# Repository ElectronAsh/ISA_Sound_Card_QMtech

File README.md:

# FPGA-based ISA Sound Card

Warning: Please don't build this yet. It's not 100% done, and no PCBs have been ordered yet.

The idea here is to leverage the Sound Blaster 16 and OPL Verilog from the ao486 project to use on an ISA card.
In theory, it shouldn't take too much effort to adapt that logic to run on a "real" ISA bus, but I may be speaking too soon. lol

(ao486 and OPL3 cores by Aleksander Osman. Improvements by Sorgelig, Robert Piep, and many others.) 

This version is using the Cyclone IV module from QMtech...

https://www.aliexpress.com/item/32949281189.html

This is mainly due to the current chip shortage, and there aren't many of the QMtech boards left in stock either.

If/when the chip shortage improves, the FPGA can be put directly onto the ISA card.

There are some sellers on AliExpress who have the very same FPGA available, but their stock levels also might be quite low.

Using the QMtech board does save from having to do the BGA routing for the FPGA, and the routing for the SDRAM.
The modules also have switching regulators onboard, for the FPGA and 3V3 rails.

The SDRAM will be useful for trying my old Wavetable MIDI synth later.

Shoutout to the RMC crew on Discord. ;)

ElectronAsh

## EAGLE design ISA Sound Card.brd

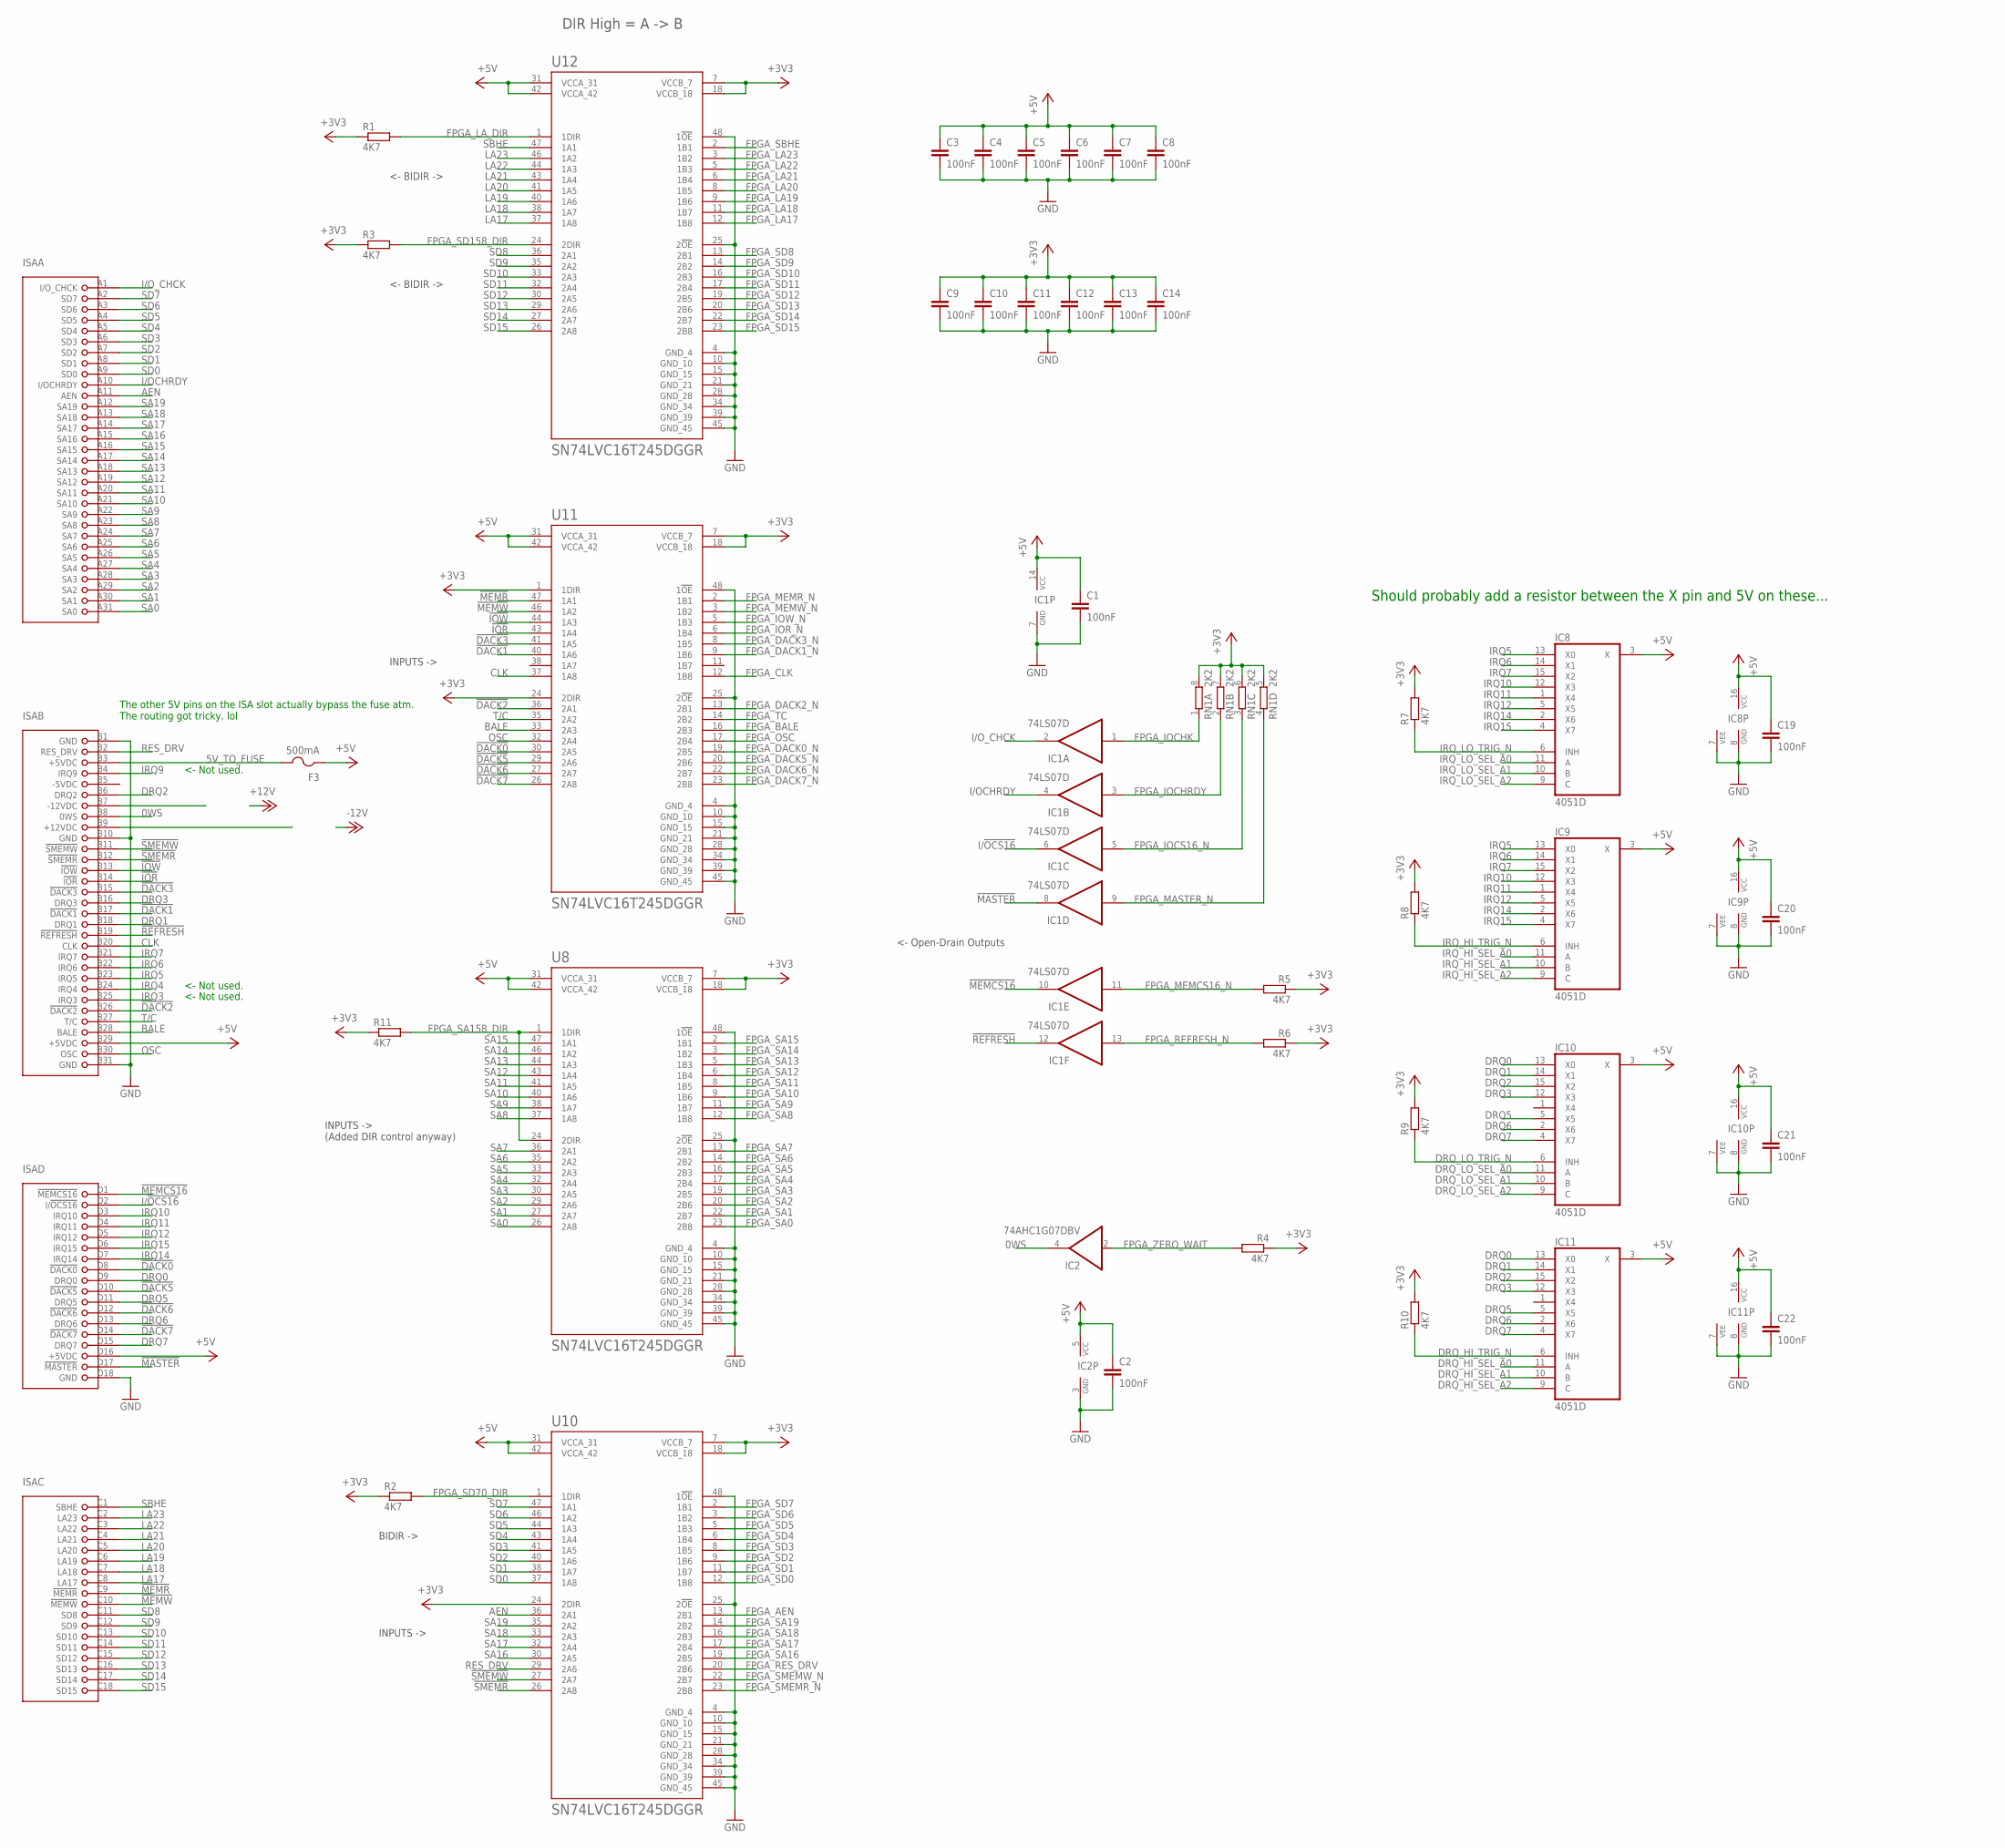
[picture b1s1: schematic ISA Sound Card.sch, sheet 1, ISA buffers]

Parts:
C1, C2, C3, C4, C5, C6, C7, C8, C9, C10, C11, C12, C13, C14, C19, C20, C21, C22: 100nF; C0603
F3: 500mA; R1206
IC1: 74LS07D; SO14
IC2: 74AHC1G07DBV; SOT23-5
IC8, IC9, IC10, IC11: 4051D; SO16
ISA: IBMATBUS; IBM-AT
R1, R2, R3, R4, R5, R6, R7, R8, R9, R10, R11: 4K7; R0603
RN1: 2K2; 0603-ARC
U8, U10, U11, U12: SN74LVC16T245DGGR; SOP50P810X120-48N

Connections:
0WS: IC2.4 (O), ISA.B8 (0WS)
5V_TO_FUSE: F3.2, ISA.B3 (+5VDC)
!DACK0: ISA.D8 (!DACK0), U11.30 (2A5)
!DACK1: ISA.B17 (!DACK1), U11.40 (1A6)
!DACK2: ISA.B26 (!DACK2), U11.36 (2A1)
!DACK3: ISA.B15 (!DACK3), U11.41 (1A5)
!DACK5: ISA.D10 (!DACK5), U11.29 (2A6)
!DACK6: ISA.D12 (!DACK6), U11.27 (2A7)
!DACK7: ISA.D14 (!DACK7), U11.26 (2A8)
!IOR: ISA.B14 (!IOR), U11.43 (1A4)
!IOW: ISA.B13 (!IOW), U11.44 (1A3)
!MASTER: IC1.8 (O), ISA.D17 (!MASTER)
!MEMCS16: IC1.10 (O), ISA.D1 (!MEMCS16)
!MEMR: ISA.C9 (!MEMR), U11.47 (1A1)
!MEMW: ISA.C10 (!MEMW), U11.46 (1A2)
!REFRESH: IC1.12 (O), ISA.B19 (!REFRESH)
!SMEMR: ISA.B12 (!SMEMR), U10.26 (2A8)
!SMEMW: ISA.B11 (!SMEMW), U10.27 (2A7)
+3V3: C9.1, C10.1, C11.1, C12.1, C13.1, C14.1, R1.1, R2.1, R3.1, R4.1, R5.1, R6.1, R7.2, R8.2, R9.2, R10.2, R11.1, RN1.5 (2), RN1.6 (2), RN1.7 (2), RN1.8 (2), U8.7 (VCCB_7), U8.18 (VCCB_18), U10.7 (VCCB_7), U10.18 (VCCB_18), U10.24 (2DIR), U11.1 (1DIR), U11.7 (VCCB_7), U11.18 (VCCB_18), U11.24 (2DIR), U12.7 (VCCB_7), U12.18 (VCCB_18); also elsewhere on the board
+5V: C1.1, C2.1, C3.1, C4.1, C5.1, C6.1, C7.1, C8.1, C19.1, C20.1, C21.1, C22.1, F3.1, IC1.14 (VCC), IC2.5 (VCC), IC8.3 (X), IC8.16 (VCC), IC9.3 (X), IC9.16 (VCC), IC10.3 (X), IC10.16 (VCC), IC11.3 (X), IC11.16 (VCC), ISA.B29 (+5VDC), ISA.D16 (+5VDC), U8.31 (VCCA_31), U8.42 (VCCA_42), U10.31 (VCCA_31), U10.42 (VCCA_42), U11.31 (VCCA_31), U11.42 (VCCA_42), U12.31 (VCCA_31), U12.42 (VCCA_42); also elsewhere on the board
-5VDC: ISA.B5 (-5VDC)
AEN: ISA.A11 (AEN), U10.36 (2A1)
BALE: ISA.B28 (BALE), U11.33 (2A3)
CLK: ISA.B20 (CLK), U11.37 (1A8)
DRQ0: IC10.13 (X0), IC11.13 (X0), ISA.D9 (DRQ0)
DRQ1: IC10.14 (X1), IC11.14 (X1), ISA.B18 (DRQ1)
DRQ2: IC10.15 (X2), IC11.15 (X2), ISA.B6 (DRQ2)
DRQ3: IC10.12 (X3), IC11.12 (X3), ISA.B16 (DRQ3)
DRQ5: IC10.5 (X5), IC11.5 (X5), ISA.D11 (DRQ5)
DRQ6: IC10.2 (X6), IC11.2 (X6), ISA.D13 (DRQ6)
DRQ7: IC10.4 (X7), IC11.4 (X7), ISA.D15 (DRQ7)
DRQ_HI_SEL_A0: IC11.11 (A); also elsewhere on the board
DRQ_HI_SEL_A1: IC11.10 (B); also elsewhere on the board
DRQ_HI_SEL_A2: IC11.9 (C); also elsewhere on the board
DRQ_HI_TRIG_N: IC11.6 (INH), R10.1; also elsewhere on the board
DRQ_LO_SEL_A0: IC10.11 (A); also elsewhere on the board
DRQ_LO_SEL_A1: IC10.10 (B); also elsewhere on the board
DRQ_LO_SEL_A2: IC10.9 (C); also elsewhere on the board
DRQ_LO_TRIG_N: IC10.6 (INH), R9.1; also elsewhere on the board
FPGA_AEN: U10.13 (2B1); also elsewhere on the board
FPGA_BALE: U11.16 (2B3); also elsewhere on the board
FPGA_CLK: U11.12 (1B8); also elsewhere on the board
FPGA_DACK0_N: U11.19 (2B5); also elsewhere on the board
FPGA_DACK1_N: U11.9 (1B6); also elsewhere on the board
FPGA_DACK2_N: U11.13 (2B1); also elsewhere on the board
FPGA_DACK3_N: U11.8 (1B5); also elsewhere on the board
FPGA_DACK5_N: U11.20 (2B6); also elsewhere on the board
FPGA_DACK6_N: U11.22 (2B7); also elsewhere on the board
FPGA_DACK7_N: U11.23 (2B8); also elsewhere on the board
FPGA_IOCHK: IC1.1 (I), RN1.1; also elsewhere on the board
FPGA_IOCHRDY: IC1.3 (I), RN1.2 (1); also elsewhere on the board
FPGA_IOCS16_N: IC1.5 (I), RN1.3 (1); also elsewhere on the board
FPGA_IOR_N: U11.6 (1B4); also elsewhere on the board
FPGA_IOW_N: U11.5 (1B3); also elsewhere on the board
FPGA_LA17: U12.12 (1B8); also elsewhere on the board
FPGA_LA18: U12.11 (1B7); also elsewhere on the board
FPGA_LA19: U12.9 (1B6); also elsewhere on the board
FPGA_LA20: U12.8 (1B5); also elsewhere on the board
FPGA_LA21: U12.6 (1B4); also elsewhere on the board
FPGA_LA22: U12.5 (1B3); also elsewhere on the board
FPGA_LA23: U12.3 (1B2); also elsewhere on the board
FPGA_LA_DIR: R1.2, U12.1 (1DIR); also elsewhere on the board
FPGA_MASTER_N: IC1.9 (I), RN1.4 (1); also elsewhere on the board
FPGA_MEMCS16_N: IC1.11 (I), R5.2; also elsewhere on the board
FPGA_MEMR_N: U11.2 (1B1); also elsewhere on the board
FPGA_MEMW_N: U11.3 (1B2); also elsewhere on the board
FPGA_OSC: U11.17 (2B4); also elsewhere on the board
FPGA_REFRESH_N: IC1.13 (I), R6.2; also elsewhere on the board
FPGA_RES_DRV: U10.20 (2B6); also elsewhere on the board
FPGA_SA0: U8.23 (2B8); also elsewhere on the board
FPGA_SA1: U8.22 (2B7); also elsewhere on the board
FPGA_SA2: U8.20 (2B6); also elsewhere on the board
FPGA_SA3: U8.19 (2B5); also elsewhere on the board
FPGA_SA4: U8.17 (2B4); also elsewhere on the board
FPGA_SA5: U8.16 (2B3); also elsewhere on the board
FPGA_SA6: U8.14 (2B2); also elsewhere on the board
FPGA_SA7: U8.13 (2B1); also elsewhere on the board
FPGA_SA8: U8.12 (1B8); also elsewhere on the board
FPGA_SA9: U8.11 (1B7); also elsewhere on the board
FPGA_SA10: U8.9 (1B6); also elsewhere on the board
FPGA_SA11: U8.8 (1B5); also elsewhere on the board
FPGA_SA12: U8.6 (1B4); also elsewhere on the board
FPGA_SA13: U8.5 (1B3); also elsewhere on the board
FPGA_SA14: U8.3 (1B2); also elsewhere on the board
FPGA_SA15: U8.2 (1B1); also elsewhere on the board
FPGA_SA16: U10.19 (2B5); also elsewhere on the board
FPGA_SA17: U10.17 (2B4); also elsewhere on the board
FPGA_SA18: U10.16 (2B3); also elsewhere on the board
FPGA_SA19: U10.14 (2B2); also elsewhere on the board
FPGA_SA158_DIR: R11.2, U8.1 (1DIR), U8.24 (2DIR); also elsewhere on the board
FPGA_SBHE: U12.2 (1B1); also elsewhere on the board
FPGA_SD0: U10.12 (1B8); also elsewhere on the board
FPGA_SD1: U10.11 (1B7); also elsewhere on the board
FPGA_SD2: U10.9 (1B6); also elsewhere on the board
FPGA_SD3: U10.8 (1B5); also elsewhere on the board
FPGA_SD4: U10.6 (1B4); also elsewhere on the board
FPGA_SD5: U10.5 (1B3); also elsewhere on the board
FPGA_SD6: U10.3 (1B2); also elsewhere on the board
FPGA_SD7: U10.2 (1B1); also elsewhere on the board
FPGA_SD8: U12.13 (2B1); also elsewhere on the board
FPGA_SD9: U12.14 (2B2); also elsewhere on the board
FPGA_SD10: U12.16 (2B3); also elsewhere on the board
FPGA_SD11: U12.17 (2B4); also elsewhere on the board
FPGA_SD12: U12.19 (2B5); also elsewhere on the board
FPGA_SD13: U12.20 (2B6); also elsewhere on the board
FPGA_SD14: U12.22 (2B7); also elsewhere on the board
FPGA_SD15: U12.23 (2B8); also elsewhere on the board
FPGA_SD70_DIR: R2.2, U10.1 (1DIR); also elsewhere on the board
FPGA_SD158_DIR: R3.2, U12.24 (2DIR); also elsewhere on the board
FPGA_SMEMR_N: U10.23 (2B8); also elsewhere on the board
FPGA_SMEMW_N: U10.22 (2B7); also elsewhere on the board
FPGA_TC: U11.14 (2B2); also elsewhere on the board
FPGA_ZERO_WAIT: IC2.2 (I), R4.2; also elsewhere on the board
GND: C1.2, C2.2, C3.2, C4.2, C5.2, C6.2, C7.2, C8.2, C9.2, C10.2, C11.2, C12.2, C13.2, C14.2, C19.2, C20.2, C21.2, C22.2, IC1.7 (GND), IC2.3 (GND), IC8.7 (VEE), IC8.8 (GND), IC9.7 (VEE), IC9.8 (GND), IC10.7 (VEE), IC10.8 (GND), IC11.7 (VEE), IC11.8 (GND), ISA.B1 (GND), ISA.B10 (GND), ISA.B31 (GND), ISA.D18 (GND), U8.4 (GND_4), U8.10 (GND_10), U8.15 (GND_15), U8.21 (GND_21), U8.25 (2!OE), U8.28 (GND_28), U8.34 (GND_34), U8.39 (GND_39), U8.45 (GND_45), U8.48 (1!OE), U10.4 (GND_4), U10.10 (GND_10), U10.15 (GND_15), U10.21 (GND_21), U10.25 (2!OE), U10.28 (GND_28), U10.34 (GND_34), U10.39 (GND_39), U10.45 (GND_45), U10.48 (1!OE), U11.4 (GND_4), U11.10 (GND_10), U11.15 (GND_15), U11.21 (GND_21), U11.25 (2!OE), U11.28 (GND_28), U11.34 (GND_34), U11.39 (GND_39), U11.45 (GND_45), U11.48 (1!OE), U12.4 (GND_4), U12.10 (GND_10), U12.15 (GND_15), U12.21 (GND_21), U12.25 (2!OE), U12.28 (GND_28), U12.34 (GND_34), U12.39 (GND_39), U12.45 (GND_45), U12.48 (1!OE); also elsewhere on the board
I/!OCS16: IC1.6 (O), ISA.D2 (I/!OCS16)
I/OCHRDY: IC1.4 (O), ISA.A10 (I/OCHRDY)
I/O_CHCK: IC1.2 (O), ISA.A1 (I/O_CHCK)
IRQ3: ISA.B25 (IRQ3)
IRQ4: ISA.B24 (IRQ4)
IRQ5: IC8.13 (X0), IC9.13 (X0), ISA.B23 (IRQ5)
IRQ6: IC8.14 (X1), IC9.14 (X1), ISA.B22 (IRQ6)
IRQ7: IC8.15 (X2), IC9.15 (X2), ISA.B21 (IRQ7)
IRQ9: ISA.B4 (IRQ9)
IRQ10: IC8.12 (X3), IC9.12 (X3), ISA.D3 (IRQ10)
IRQ11: IC8.1 (X4), IC9.1 (X4), ISA.D4 (IRQ11)
IRQ12: IC8.5 (X5), IC9.5 (X5), ISA.D5 (IRQ12)
IRQ14: IC8.2 (X6), IC9.2 (X6), ISA.D7 (IRQ14)
IRQ15: IC8.4 (X7), IC9.4 (X7), ISA.D6 (IRQ15)
IRQ_HI_SEL_A0: IC9.11 (A); also elsewhere on the board
IRQ_HI_SEL_A1: IC9.10 (B); also elsewhere on the board
IRQ_HI_SEL_A2: IC9.9 (C); also elsewhere on the board
IRQ_HI_TRIG_N: IC9.6 (INH), R8.1; also elsewhere on the board
IRQ_LO_SEL_A0: IC8.11 (A); also elsewhere on the board
IRQ_LO_SEL_A1: IC8.10 (B); also elsewhere on the board
IRQ_LO_SEL_A2: IC8.9 (C); also elsewhere on the board
IRQ_LO_TRIG_N: IC8.6 (INH), R7.1; also elsewhere on the board
LA17: ISA.C8 (LA17), U12.37 (1A8)
LA18: ISA.C7 (LA18), U12.38 (1A7)
LA19: ISA.C6 (LA19), U12.40 (1A6)
LA20: ISA.C5 (LA20), U12.41 (1A5)
LA21: ISA.C4 (LA21), U12.43 (1A4)
LA22: ISA.C3 (LA22), U12.44 (1A3)
LA23: ISA.C2 (LA23), U12.46 (1A2)
OSC: ISA.B30 (OSC), U11.32 (2A4)
RES_DRV: ISA.B2 (RES_DRV), U10.29 (2A6)
SA0: ISA.A31 (SA0), U8.26 (2A8)
SA1: ISA.A30 (SA1), U8.27 (2A7)
SA2: ISA.A29 (SA2), U8.29 (2A6)
SA3: ISA.A28 (SA3), U8.30 (2A5)
SA4: ISA.A27 (SA4), U8.32 (2A4)
SA5: ISA.A26 (SA5), U8.33 (2A3)
SA6: ISA.A25 (SA6), U8.35 (2A2)
SA7: ISA.A24 (SA7), U8.36 (2A1)
SA8: ISA.A23 (SA8), U8.37 (1A8)
SA9: ISA.A22 (SA9), U8.38 (1A7)
SA10: ISA.A21 (SA10), U8.40 (1A6)
SA11: ISA.A20 (SA11), U8.41 (1A5)
SA12: ISA.A19 (SA12), U8.43 (1A4)
SA13: ISA.A18 (SA13), U8.44 (1A3)
SA14: ISA.A17 (SA14), U8.46 (1A2)
SA15: ISA.A16 (SA15), U8.47 (1A1)
SA16: ISA.A15 (SA16), U10.30 (2A5)
SA17: ISA.A14 (SA17), U10.32 (2A4)
SA18: ISA.A13 (SA18), U10.33 (2A3)
SA19: ISA.A12 (SA19), U10.35 (2A2)
SBHE: ISA.C1 (SBHE), U12.47 (1A1)
SD0: ISA.A9 (SD0), U10.37 (1A8)
SD1: ISA.A8 (SD1), U10.38 (1A7)
SD2: ISA.A7 (SD2), U10.40 (1A6)
SD3: ISA.A6 (SD3), U10.41 (1A5)
SD4: ISA.A5 (SD4), U10.43 (1A4)
SD5: ISA.A4 (SD5), U10.44 (1A3)
SD6: ISA.A3 (SD6), U10.46 (1A2)
SD7: ISA.A2 (SD7), U10.47 (1A1)
SD8: ISA.C11 (SD8), U12.36 (2A1)
SD9: ISA.C12 (SD9), U12.35 (2A2)
SD10: ISA.C13 (SD10), U12.33 (2A3)
SD11: ISA.C14 (SD11), U12.32 (2A4)
SD12: ISA.C15 (SD12), U12.30 (2A5)
SD13: ISA.C16 (SD13), U12.29 (2A6)
SD14: ISA.C17 (SD14), U12.27 (2A7)
SD15: ISA.C18 (SD15), U12.26 (2A8)
T/C: ISA.B27 (T/C), U11.35 (2A2)

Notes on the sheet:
INPUTS -> (Added DIR control anyway)
BIDIR ->
INPUTS ->
<- BIDIR ->
DIR High = A -> B
<- Open-Drain Outputs
Should probably add a resistor between the X pin and 5V on these...
The other 5V pins on the ISA slot actually bypass the fuse atm. The routing got tricky. lol
<- Not used.

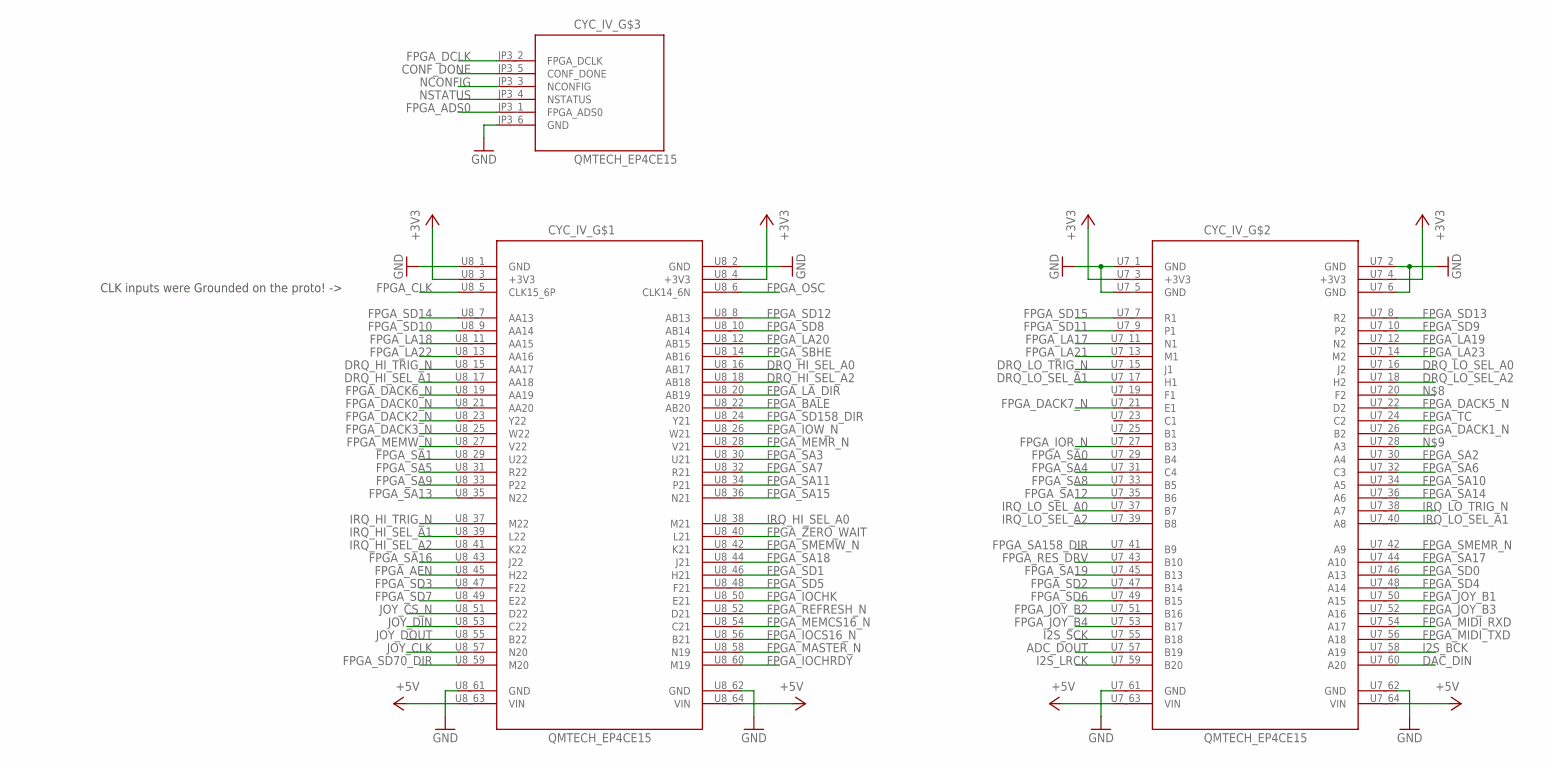
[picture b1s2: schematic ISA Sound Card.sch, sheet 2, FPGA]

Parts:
CYC_IV_: QMTECH_EP4CE15; QMTECH_EP4CE15_SMD

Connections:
+3V3: CYC_IV_.U7_3 (+3V3), CYC_IV_.U7_4 (+3V3), CYC_IV_.U8_3 (+3V3), CYC_IV_.U8_4 (+3V3); also elsewhere on the board
+5V: CYC_IV_.U7_63 (VIN), CYC_IV_.U7_64 (VIN), CYC_IV_.U8_63 (VIN), CYC_IV_.U8_64 (VIN); also elsewhere on the board
ADC_DOUT: CYC_IV_.U7_57 (B19); also elsewhere on the board
CONF_DONE: CYC_IV_.JP3_5 (CONF_DONE)
DAC_DIN: CYC_IV_.U7_60 (A20); also elsewhere on the board
DRQ_HI_SEL_A0: CYC_IV_.U8_16 (AB17); also elsewhere on the board
DRQ_HI_SEL_A1: CYC_IV_.U8_17 (AA18); also elsewhere on the board
DRQ_HI_SEL_A2: CYC_IV_.U8_18 (AB18); also elsewhere on the board
DRQ_HI_TRIG_N: CYC_IV_.U8_15 (AA17); also elsewhere on the board
DRQ_LO_SEL_A0: CYC_IV_.U7_16 (J2); also elsewhere on the board
DRQ_LO_SEL_A1: CYC_IV_.U7_17 (H1); also elsewhere on the board
DRQ_LO_SEL_A2: CYC_IV_.U7_18 (H2); also elsewhere on the board
DRQ_LO_TRIG_N: CYC_IV_.U7_15 (J1); also elsewhere on the board
FPGA_ADS0: CYC_IV_.JP3_1 (FPGA_ADS0)
FPGA_AEN: CYC_IV_.U8_45 (H22); also elsewhere on the board
FPGA_BALE: CYC_IV_.U8_22 (AB20); also elsewhere on the board
FPGA_CLK: CYC_IV_.U8_5 (CLK15_6P); also elsewhere on the board
FPGA_DACK0_N: CYC_IV_.U8_21 (AA20); also elsewhere on the board
FPGA_DACK1_N: CYC_IV_.U7_26 (B2); also elsewhere on the board
FPGA_DACK2_N: CYC_IV_.U8_23 (Y22); also elsewhere on the board
FPGA_DACK3_N: CYC_IV_.U8_25 (W22); also elsewhere on the board
FPGA_DACK5_N: CYC_IV_.U7_22 (D2); also elsewhere on the board
FPGA_DACK6_N: CYC_IV_.U8_19 (AA19); also elsewhere on the board
FPGA_DACK7_N: CYC_IV_.U7_21 (E1); also elsewhere on the board
FPGA_DCLK: CYC_IV_.JP3_2 (FPGA_DCLK)
FPGA_IOCHK: CYC_IV_.U8_50 (E21); also elsewhere on the board
FPGA_IOCHRDY: CYC_IV_.U8_60 (M19); also elsewhere on the board
FPGA_IOCS16_N: CYC_IV_.U8_56 (B21); also elsewhere on the board
FPGA_IOR_N: CYC_IV_.U7_27 (B3); also elsewhere on the board
FPGA_IOW_N: CYC_IV_.U8_26 (W21); also elsewhere on the board
FPGA_JOY_B1: CYC_IV_.U7_50 (A15); also elsewhere on the board
FPGA_JOY_B2: CYC_IV_.U7_51 (B16); also elsewhere on the board
FPGA_JOY_B3: CYC_IV_.U7_52 (A16); also elsewhere on the board
FPGA_JOY_B4: CYC_IV_.U7_53 (B17); also elsewhere on the board
FPGA_LA17: CYC_IV_.U7_11 (N1); also elsewhere on the board
FPGA_LA18: CYC_IV_.U8_11 (AA15); also elsewhere on the board
FPGA_LA19: CYC_IV_.U7_12 (N2); also elsewhere on the board
FPGA_LA20: CYC_IV_.U8_12 (AB15); also elsewhere on the board
FPGA_LA21: CYC_IV_.U7_13 (M1); also elsewhere on the board
FPGA_LA22: CYC_IV_.U8_13 (AA16); also elsewhere on the board
FPGA_LA23: CYC_IV_.U7_14 (M2); also elsewhere on the board
FPGA_LA_DIR: CYC_IV_.U8_20 (AB19); also elsewhere on the board
FPGA_MASTER_N: CYC_IV_.U8_58 (N19); also elsewhere on the board
FPGA_MEMCS16_N: CYC_IV_.U8_54 (C21); also elsewhere on the board
FPGA_MEMR_N: CYC_IV_.U8_28 (V21); also elsewhere on the board
FPGA_MEMW_N: CYC_IV_.U8_27 (V22); also elsewhere on the board
FPGA_MIDI_RXD: CYC_IV_.U7_54 (A17); also elsewhere on the board
FPGA_MIDI_TXD: CYC_IV_.U7_56 (A18); also elsewhere on the board
FPGA_OSC: CYC_IV_.U8_6 (CLK14_6N); also elsewhere on the board
FPGA_REFRESH_N: CYC_IV_.U8_52 (D21); also elsewhere on the board
FPGA_RES_DRV: CYC_IV_.U7_43 (B10); also elsewhere on the board
FPGA_SA0: CYC_IV_.U7_29 (B4); also elsewhere on the board
FPGA_SA1: CYC_IV_.U8_29 (U22); also elsewhere on the board
FPGA_SA2: CYC_IV_.U7_30 (A4); also elsewhere on the board
FPGA_SA3: CYC_IV_.U8_30 (U21); also elsewhere on the board
FPGA_SA4: CYC_IV_.U7_31 (C4); also elsewhere on the board
FPGA_SA5: CYC_IV_.U8_31 (R22); also elsewhere on the board
FPGA_SA6: CYC_IV_.U7_32 (C3); also elsewhere on the board
FPGA_SA7: CYC_IV_.U8_32 (R21); also elsewhere on the board
FPGA_SA8: CYC_IV_.U7_33 (B5); also elsewhere on the board
FPGA_SA9: CYC_IV_.U8_33 (P22); also elsewhere on the board
FPGA_SA10: CYC_IV_.U7_34 (A5); also elsewhere on the board
FPGA_SA11: CYC_IV_.U8_34 (P21); also elsewhere on the board
FPGA_SA12: CYC_IV_.U7_35 (B6); also elsewhere on the board
FPGA_SA13: CYC_IV_.U8_35 (N22); also elsewhere on the board
FPGA_SA14: CYC_IV_.U7_36 (A6); also elsewhere on the board
FPGA_SA15: CYC_IV_.U8_36 (N21); also elsewhere on the board
FPGA_SA16: CYC_IV_.U8_43 (J22); also elsewhere on the board
FPGA_SA17: CYC_IV_.U7_44 (A10); also elsewhere on the board
FPGA_SA18: CYC_IV_.U8_44 (J21); also elsewhere on the board
FPGA_SA19: CYC_IV_.U7_45 (B13); also elsewhere on the board
FPGA_SA158_DIR: CYC_IV_.U7_41 (B9); also elsewhere on the board
FPGA_SBHE: CYC_IV_.U8_14 (AB16); also elsewhere on the board
FPGA_SD0: CYC_IV_.U7_46 (A13); also elsewhere on the board
FPGA_SD1: CYC_IV_.U8_46 (H21); also elsewhere on the board
FPGA_SD2: CYC_IV_.U7_47 (B14); also elsewhere on the board
FPGA_SD3: CYC_IV_.U8_47 (F22); also elsewhere on the board
FPGA_SD4: CYC_IV_.U7_48 (A14); also elsewhere on the board
FPGA_SD5: CYC_IV_.U8_48 (F21); also elsewhere on the board
FPGA_SD6: CYC_IV_.U7_49 (B15); also elsewhere on the board
FPGA_SD7: CYC_IV_.U8_49 (E22); also elsewhere on the board
FPGA_SD8: CYC_IV_.U8_10 (AB14); also elsewhere on the board
FPGA_SD9: CYC_IV_.U7_10 (P2); also elsewhere on the board
FPGA_SD10: CYC_IV_.U8_9 (AA14); also elsewhere on the board
FPGA_SD11: CYC_IV_.U7_9 (P1); also elsewhere on the board
FPGA_SD12: CYC_IV_.U8_8 (AB13); also elsewhere on the board
FPGA_SD13: CYC_IV_.U7_8 (R2); also elsewhere on the board
FPGA_SD14: CYC_IV_.U8_7 (AA13); also elsewhere on the board
FPGA_SD15: CYC_IV_.U7_7 (R1); also elsewhere on the board
FPGA_SD70_DIR: CYC_IV_.U8_59 (M20); also elsewhere on the board
FPGA_SD158_DIR: CYC_IV_.U8_24 (Y21); also elsewhere on the board
FPGA_SMEMR_N: CYC_IV_.U7_42 (A9); also elsewhere on the board
FPGA_SMEMW_N: CYC_IV_.U8_42 (K21); also elsewhere on the board
FPGA_TC: CYC_IV_.U7_24 (C2); also elsewhere on the board
FPGA_ZERO_WAIT: CYC_IV_.U8_40 (L21); also elsewhere on the board
GND: CYC_IV_.JP3_6 (GND), CYC_IV_.U7_1 (GND), CYC_IV_.U7_2 (GND), CYC_IV_.U7_5 (GND), CYC_IV_.U7_6 (GND), CYC_IV_.U7_61 (GND), CYC_IV_.U7_62 (GND), CYC_IV_.U8_1 (GND), CYC_IV_.U8_2 (GND), CYC_IV_.U8_61 (GND), CYC_IV_.U8_62 (GND); also elsewhere on the board
I2S_BCK: CYC_IV_.U7_58 (A19); also elsewhere on the board
I2S_LRCK: CYC_IV_.U7_59 (B20); also elsewhere on the board
I2S_SCK: CYC_IV_.U7_55 (B18); also elsewhere on the board
IRQ_HI_SEL_A0: CYC_IV_.U8_38 (M21); also elsewhere on the board
IRQ_HI_SEL_A1: CYC_IV_.U8_39 (L22); also elsewhere on the board
IRQ_HI_SEL_A2: CYC_IV_.U8_41 (K22); also elsewhere on the board
IRQ_HI_TRIG_N: CYC_IV_.U8_37 (M22); also elsewhere on the board
IRQ_LO_SEL_A0: CYC_IV_.U7_37 (B7); also elsewhere on the board
IRQ_LO_SEL_A1: CYC_IV_.U7_40 (A8); also elsewhere on the board
IRQ_LO_SEL_A2: CYC_IV_.U7_39 (B8); also elsewhere on the board
IRQ_LO_TRIG_N: CYC_IV_.U7_38 (A7); also elsewhere on the board
JOY_CLK: CYC_IV_.U8_57 (N20); also elsewhere on the board
JOY_CS_N: CYC_IV_.U8_51 (D22); also elsewhere on the board
JOY_DIN: CYC_IV_.U8_53 (C22); also elsewhere on the board
JOY_DOUT: CYC_IV_.U8_55 (B22); also elsewhere on the board
NCONFIG: CYC_IV_.JP3_3 (NCONFIG)
NSTATUS: CYC_IV_.JP3_4 (NSTATUS)

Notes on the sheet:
CLK inputs were Grounded on the proto! ->

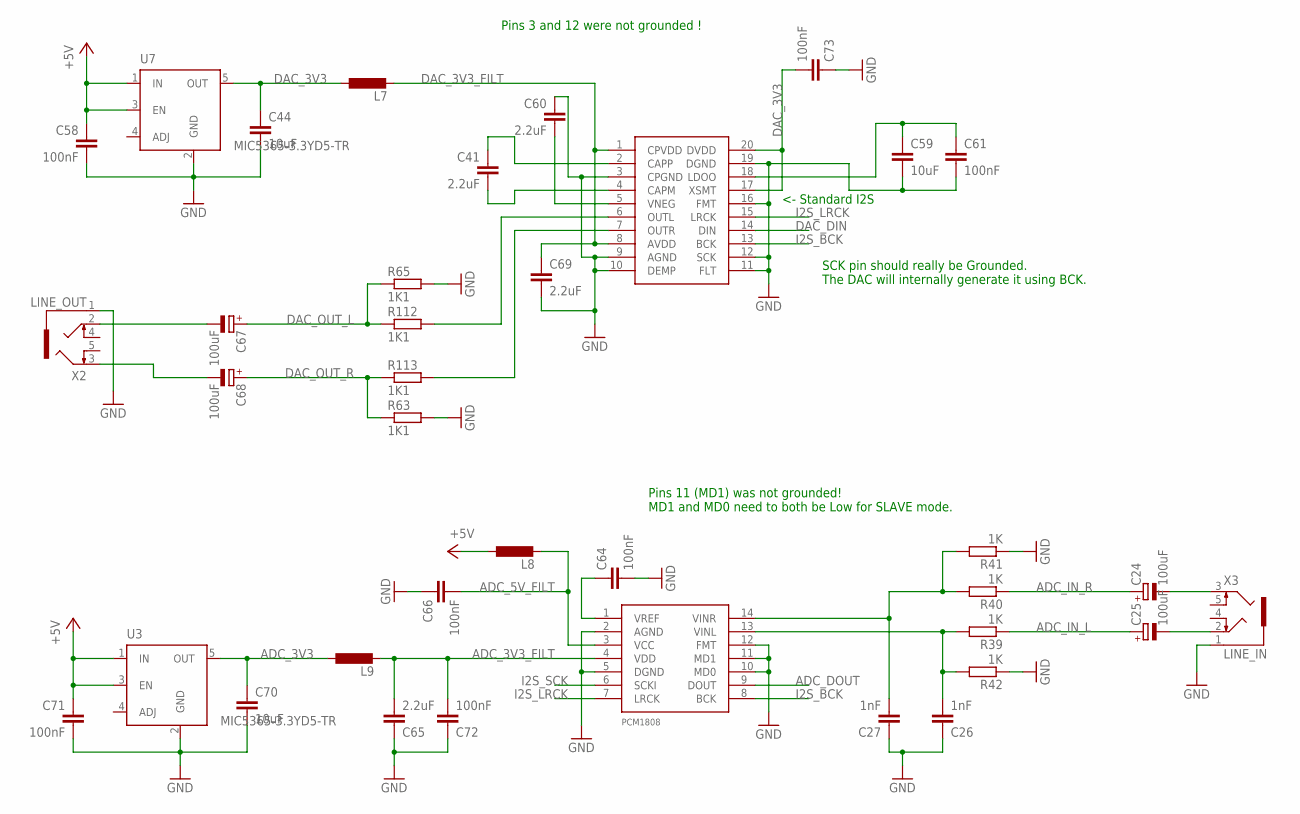
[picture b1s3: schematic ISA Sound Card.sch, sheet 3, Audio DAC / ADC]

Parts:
C24, C25, C67, C68: 100uF; PANASONIC_C
C26, C27: 1nF; C0805
C41, C60, C65, C69: 2.2uF; C0603
C44, C59, C70: 10uF; C0603
C58, C61, C66, C71, C72, C73: 100nF; C0603
C64: 100nF; C0805
L7, L8, L9: L-EUL2012C; L2012C
R39, R40, R41, R42: 1K; R0603
R63, R65, R112, R113: 1K1; R0603
U1: PCM1808; TSSOP14
U3, U7: MIC5365-3.3YD5-TR; SOT23-5
U4: PCM5102; TSSOP20
X2: LINE_OUT; 1503_09
X3: LINE_IN; 1503_09

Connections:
+5V: C58.1, C71.1, L8.1, U3.1 (IN), U3.3 (EN), U7.1 (IN), U7.3 (EN); also elsewhere on the board
ADC_3V3: C70.1, L9.1, U3.5 (OUT)
ADC_3V3_FILT: C65.2, C72.2, L9.2, U1.4 (VDD)
ADC_5V_FILT: C66.2, L8.2, U1.3 (VCC)
ADC_DOUT: U1.9 (DOUT); also elsewhere on the board
ADC_IN_L: C25.+, R39.1
ADC_IN_R: C24.+, R40.1
DAC_3V3: C44.1, C73.2, L7.1, U4.17 (XSMT), U4.20 (DVDD), U7.5 (OUT)
DAC_3V3_FILT: C69.1, L7.2, U4.1 (CPVDD), U4.8 (AVDD)
DAC_DIN: U4.14 (DIN); also elsewhere on the board
DAC_OUT_L: C67.+, R65.1, R112.1
DAC_OUT_R: C68.+, R63.1, R113.1
GND: C26.1, C27.1, C44.2, C58.2, C59.2, C60.1, C61.2, C64.2, C65.1, C66.1, C69.2, C70.2, C71.2, C72.1, C73.1, R41.1, R42.1, R63.2, R65.2, U1.2 (AGND), U1.5 (DGND), U1.10 (MD0), U1.11 (MD1), U1.12 (FMT), U3.2 (GND), U4.3 (CPGND), U4.9 (AGND), U4.10 (DEMP), U4.11 (FLT), U4.12 (SCK), U4.16 (FMT), U4.19 (DGND), U7.2 (GND), X2.1, X3.1; also elsewhere on the board
I2S_BCK: U1.8 (BCK), U4.13 (BCK); also elsewhere on the board
I2S_LRCK: U1.7 (LRCK), U4.15 (LRCK); also elsewhere on the board
I2S_SCK: U1.6 (SCKI); also elsewhere on the board
unnamed: C24.-, X3.3
unnamed: C25.-, X3.2
unnamed: C41.2, U4.4 (CAPM)
unnamed: R113.2, U4.7 (OUTR)
unnamed: C26.2, R39.2, R42.2, U1.13 (VINL)
unnamed: C27.2, R40.2, R41.2, U1.14 (VINR)
unnamed: C64.1, U1.1 (VREF)
unnamed: C68.-, X2.3
unnamed: C67.-, X2.2
unnamed: R112.2, U4.6 (OUTL)
unnamed: C59.1, C61.1, U4.18 (LDOO)
unnamed: C41.1, U4.2 (CAPP)
unnamed: C60.2, U4.5 (VNEG)

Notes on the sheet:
<- Standard I2S
Pins 3 and 12 were not grounded !
SCK pin should really be Grounded. The DAC will internally generate it using BCK.
Pins 11 (MD1) was not grounded! MD1 and MD0 need to both be Low for SLAVE mode.

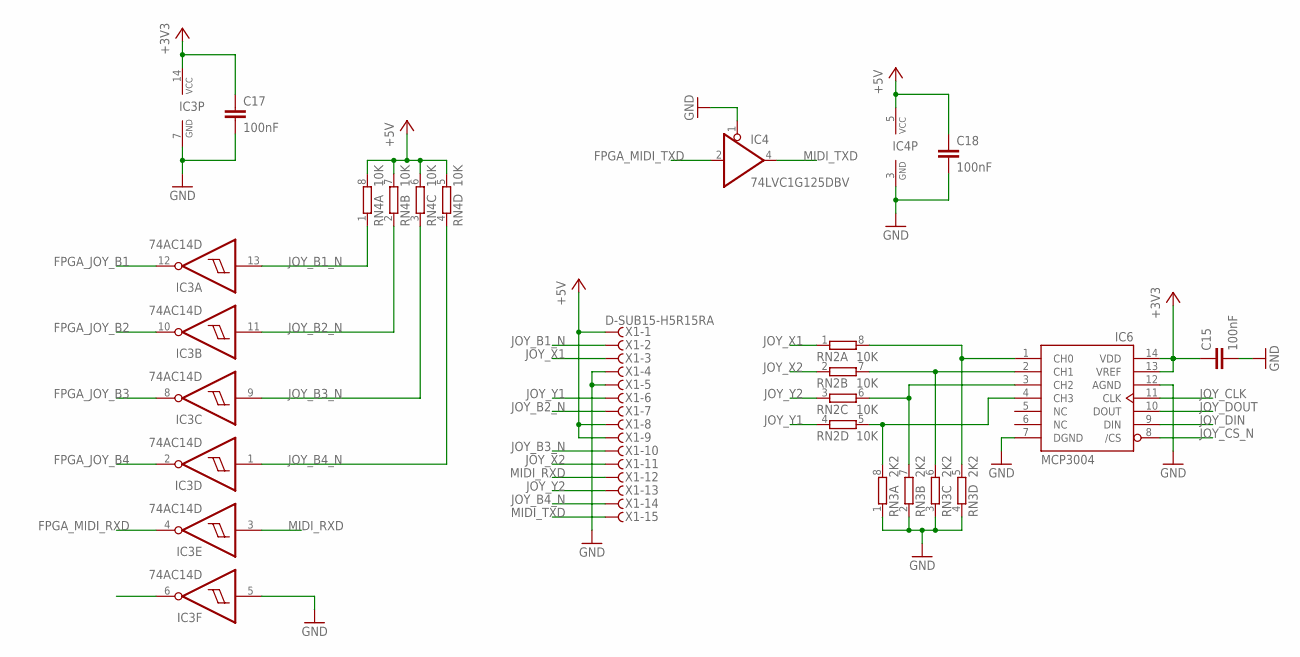
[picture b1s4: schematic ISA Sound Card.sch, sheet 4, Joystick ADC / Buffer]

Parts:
C15, C17, C18: 100nF; C0805
IC3: 74AC14D; SO14
IC4: 74LVC1G125DBV; SOT23-5
IC6: MCP3004; SO14
RN2, RN4: 10K; 0603-ARC
RN3: 2K2; 0603-ARC
X1: D-SUB15-H5R15RA; H5R15RA

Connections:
+3V3: C15.1, C17.1, IC3.14 (VCC), IC6.13 (VREF), IC6.14 (VDD); also elsewhere on the board
+5V: C18.1, IC4.5 (VCC), RN4.5 (2), RN4.6 (2), RN4.7 (2), RN4.8 (2), X1.1, X1.8, X1.9; also elsewhere on the board
FPGA_JOY_B1: IC3.12 (O); also elsewhere on the board
FPGA_JOY_B2: IC3.10 (O); also elsewhere on the board
FPGA_JOY_B3: IC3.8 (O); also elsewhere on the board
FPGA_JOY_B4: IC3.2 (O); also elsewhere on the board
FPGA_MIDI_RXD: IC3.4 (O); also elsewhere on the board
FPGA_MIDI_TXD: IC4.2 (I); also elsewhere on the board
GND: C15.2, C17.2, C18.2, IC3.5 (I), IC3.7 (GND), IC4.1 (OE), IC4.3 (GND), IC6.7 (DGND), IC6.12 (AGND), RN3.1, RN3.2 (1), RN3.3 (1), RN3.4 (1), X1.4, X1.5; also elsewhere on the board
JOY_B1_N: IC3.13 (I), RN4.1, X1.2
JOY_B2_N: IC3.11 (I), RN4.2 (1), X1.7
JOY_B3_N: IC3.9 (I), RN4.3 (1), X1.10
JOY_B4_N: IC3.1 (I), RN4.4 (1), X1.14
JOY_CLK: IC6.11 (CLK); also elsewhere on the board
JOY_CS_N: IC6.8 (/CS); also elsewhere on the board
JOY_DIN: IC6.9 (DIN); also elsewhere on the board
JOY_DOUT: IC6.10 (DOUT); also elsewhere on the board
JOY_X1: RN2.1, X1.3
JOY_X2: RN2.2 (1), X1.11
JOY_Y1: RN2.4 (1), X1.6
JOY_Y2: RN2.3 (1), X1.13
MIDI_RXD: IC3.3 (I), X1.12
MIDI_TXD: IC4.4 (O), X1.15
unnamed: IC6.4 (CH3), RN2.5 (2), RN3.8 (2)
unnamed: IC6.3 (CH2), RN2.6 (2), RN3.7 (2)
unnamed: IC6.2 (CH1), RN2.7 (2), RN3.6 (2)
unnamed: IC6.1 (CH0), RN2.8 (2), RN3.5 (2)

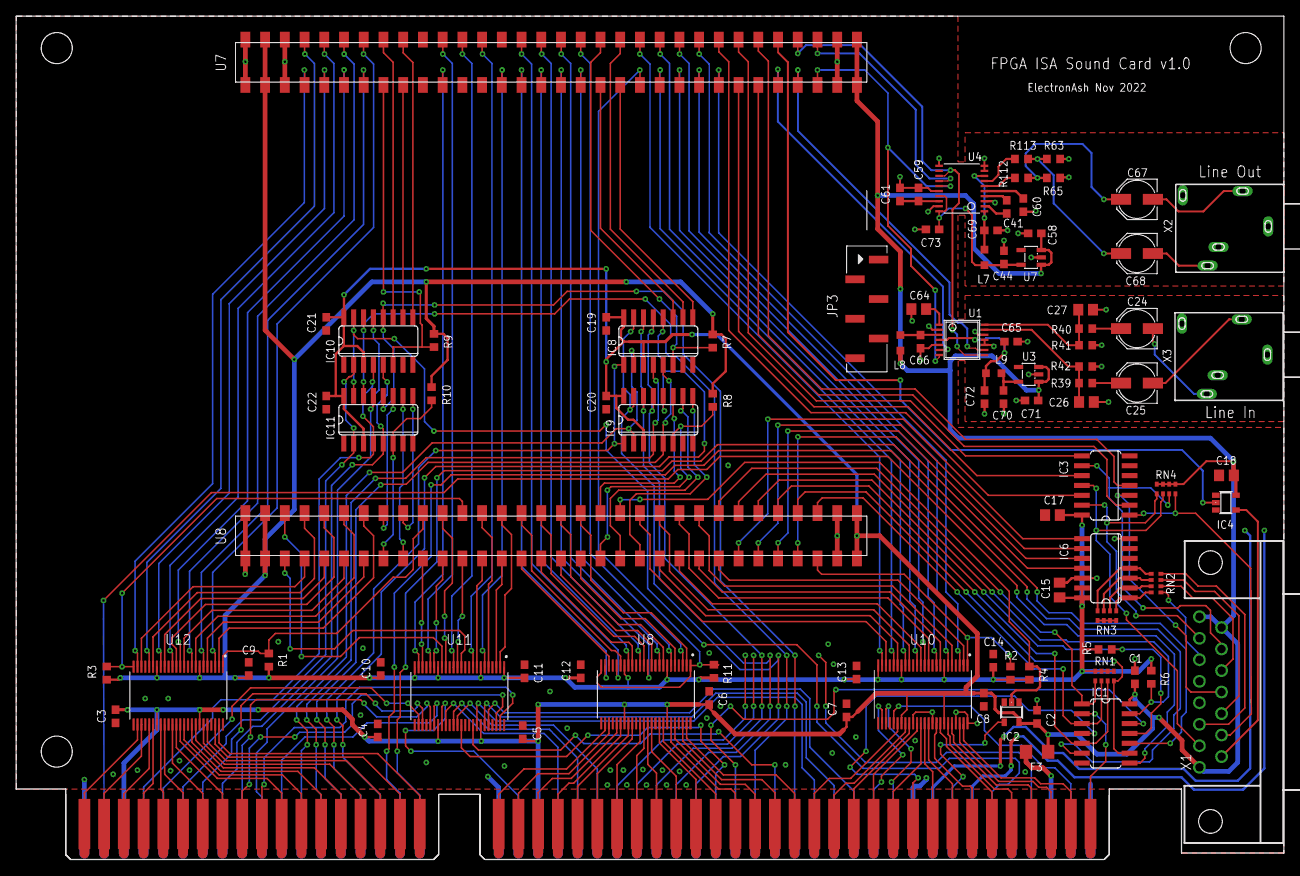
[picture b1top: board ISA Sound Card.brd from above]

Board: 2 copper layers, 163.2 x 108.6 mm, 90 parts (0 on the bottom side), 230 nets.

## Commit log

2022-10-29 Added README
2022-10-30 First routing done, DRC passed. MIDI and Waveblaster are todo
2022-11-01 Had to change IRQ/DRQ buffers for muxes. Not routed yet
2022-11-03 Routing done. Fixed two missing signals. Five proto PCBs being made by JLC
2022-11-03 Updated Eagle symbols for the QMTech CycIV version
2023-03-15 Add Quartus project
2023-03-15 OPL working well now. Sample DMA starting to work in Wolf3D
2023-03-16 Hooked up ISA CLK and OSC to the FPGA Clk-in pins
2023-03-16 Changed joystick port DB15 for the correct (female) connector
2023-03-16 Epic Pinball working in Stereo now
2023-03-18 Removed the old SDRAM stuff. Code tidy-up. Starting to add MPU. Epic Pinball working in stereo
2023-03-18 Added uart/mpu modules from ao486
2023-03-18 Removed old SDRAM PLL
2023-03-18 Fixed screach in Epic Pinball. Descent also sounds good now. Channels might be reversed?
2023-03-21 Added missing pullups to the Joystick button inputs
